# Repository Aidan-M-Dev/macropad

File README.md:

# IC Hack macropad

Six-key USB macropad with an OLED, addressable LEDs and a printable enclosure.

**Editing the appearance?** Start with the [artist handoff guide](appearance/README.md), or download the [self-contained handoff ZIP](build/appearance-handoff.zip). The [`appearance/`](appearance/) folder contains the colour config, PNG templates and image drop folder. No KiCad knowledge is needed.

The [reinforced frame](build/exports/top-frame-reinforced.stl) is the only frame version. It has **14.0 × 14.75 mm slots** (left/right × top/bottom), **6 mm straight standoffs with 0.8 mm walls**, a **flat 1 mm plate**, **2 mm links** and **2.4 mm mounting arms**. It uses the existing compact base, four **M3 × 12 mm socket-cap screws**, four M3 nuts and **no separate washers**. The flat top has no screw-head recesses; slimmer standoffs and smaller mounting pads reduce material use.

The updated [base](build/exports/base-m3x6.stl) has the USB opening's top lowered by **3 mm**, giving a **10.4 × 3.8 mm opening**. The bottom stays in place. See the [case guide](case/README.md) for connector fit and printing details.

[Exploded assembly](build/previews/top-frame-reinforced-exploded.png) · [Screw cross-section](build/previews/frame-cross-section.png) · [Printing and assembly](case/TOP-FRAME.md)

## Layout

| Folder | What belongs here |
| --- | --- |
| [`hardware/`](hardware/) | KiCad project, schematic, PCB and supplied STEP reference |
| [`case/`](case/README.md) | Enclosure CAD and presets |
| [`appearance/`](appearance/README.md) | Teammate handoff: hex colours, image drop folder and PNG guides |
| [`accessories/`](accessories/README.md) | Printable washers and M3 nut-fit tester |
| [`firmware/`](firmware/README.md) | Custom on-device software, board pin map and bring-up notes |
| `tools/` | Shared Python build, rendering and verification scripts |
| `build/` | Generated meshes, renders, reports, CAD inputs and supplier artwork |

The original ZIP is kept in `hardware/original/`. Edit the unpacked KiCad project in `hardware/`.

## Development commands

Run commands from this folder. The existing system Python packages work on this machine. For a separate environment elsewhere:

```bash
python3 -m venv .venv
. .venv/bin/activate
python -m pip install -r requirements.txt
```

The CAD workflow needs Python 3.10+, OpenSCAD, GNU Make 4.3+, and the DejaVu Sans font used by the renderer. Python requirements are listed in [`requirements.txt`](requirements.txt); firmware tools are separate.

```bash
make prepare   # Generate CAD inputs before opening OpenSCAD
make build     # Export printable parts and run exact clearance checks
make preview   # Build as needed, then refresh renders and supplier artwork
make check     # Refresh previews, then run the full design checks
make board     # Render front/back PCB images
make templates # Regenerate the artist’s PNG guides and blank canvases
make top-frame # Build and preview the reinforced switch retaining top
make firmware  # Build combined keyboard/Pong/Breakout/Doom UF2 (PlatformIO)
make firmware-clean  # Remove firmware build output; keep cached dependencies
make all       # Full design checks, board images and firmware build
```

`make` lists the commands. Set `PYTHON=/path/to/python` to use another interpreter, or `PIO=/path/to/pio` to select PlatformIO. See the [firmware installation instructions](firmware/README.md#building) before building firmware. The Makefile handles the order; PCB edits automatically refresh extracted geometry, and colour/artwork edits reuse existing meshes. Deleting a required mesh triggers a rebuild. Use `make clean` to remove generated build output, then `make all` to reproduce it. Firmware dependency caches are retained.

## What to edit

- **PCB/electronics:** open `hardware/IC Hack Macro Pad.kicad_pro`. Run `make preview` afterwards and update the firmware pin map if wiring changed. The supplied STEP file is a reference export, not automatically regenerated.
- **Enclosure dimensions:** edit `case/macropad_case.scad`, then run `make check`. Existing dimensional checks encode the current design; deliberate dimension changes may require updating their expected measurements.
- **OpenSCAD preview:** run `make prepare`, then open `case/macropad_case.scad` and select a preset. `base-m3x6.scad` opens the existing compact printable base. The reinforced frame uses M3 × 12 mm screws.
- **Accessories:** open an entry point in `accessories/`. Accessory modules share the enclosure's fastener dimensions so fit stays consistent.
- **Colours, keycap images and PCB artwork:** edit `appearance/config.json` and images in `appearance/images/`, then run `make preview`. See [appearance notes](case/APPEARANCE.md).
- **Custom software:** start in [`firmware/`](firmware/README.md); the pin map is taken from this PCB.

## Outputs

| Path | Contents |
| --- | --- |
| `firmware/.pio/build/ichack/ichack-combined.uf2` | Combined keyboard, Pong, Breakout and Doom firmware |
| `build/exports/base-m3x6.stl` | Existing compact base for the reinforced frame |
| `build/exports/top-frame-reinforced.stl` | [Reinforced retaining top; no separate washers](case/TOP-FRAME.md) |
| `build/exports/accessories/` | Printable washers and nut-fit tester |
| `build/exports/keycap.stl` | Printable keycap copied from the clicker project |
| `build/previews/` | Current frame assemblies, exploded view, cross-section and reference meshes |
| `build/exports/*-checks.json` | Verification reports |
| `build/exports/logs/` | OpenSCAD export and clearance logs |
| `build/print-pack/` | Keycap artwork, manifest and supplier CSV |
| `build/appearance-handoff.zip` | Self-contained artist handoff, also available as the `appearance/` folder |
| `build/board/` | Front/back PCB PNG and SVG |
| `build/generated/` | Extracted board datums, silkscreen and generated CAD colours |

Everything under `build/` can be regenerated. Current printable exports, previews, check reports, PCB images and the artwork pack are checked in so they can be viewed and downloaded directly. Intermediate CAD inputs, reference meshes, caches and logs are ignored. Keep source changes outside `build/`. See the [case guide](case/README.md) for printing and assembly details.

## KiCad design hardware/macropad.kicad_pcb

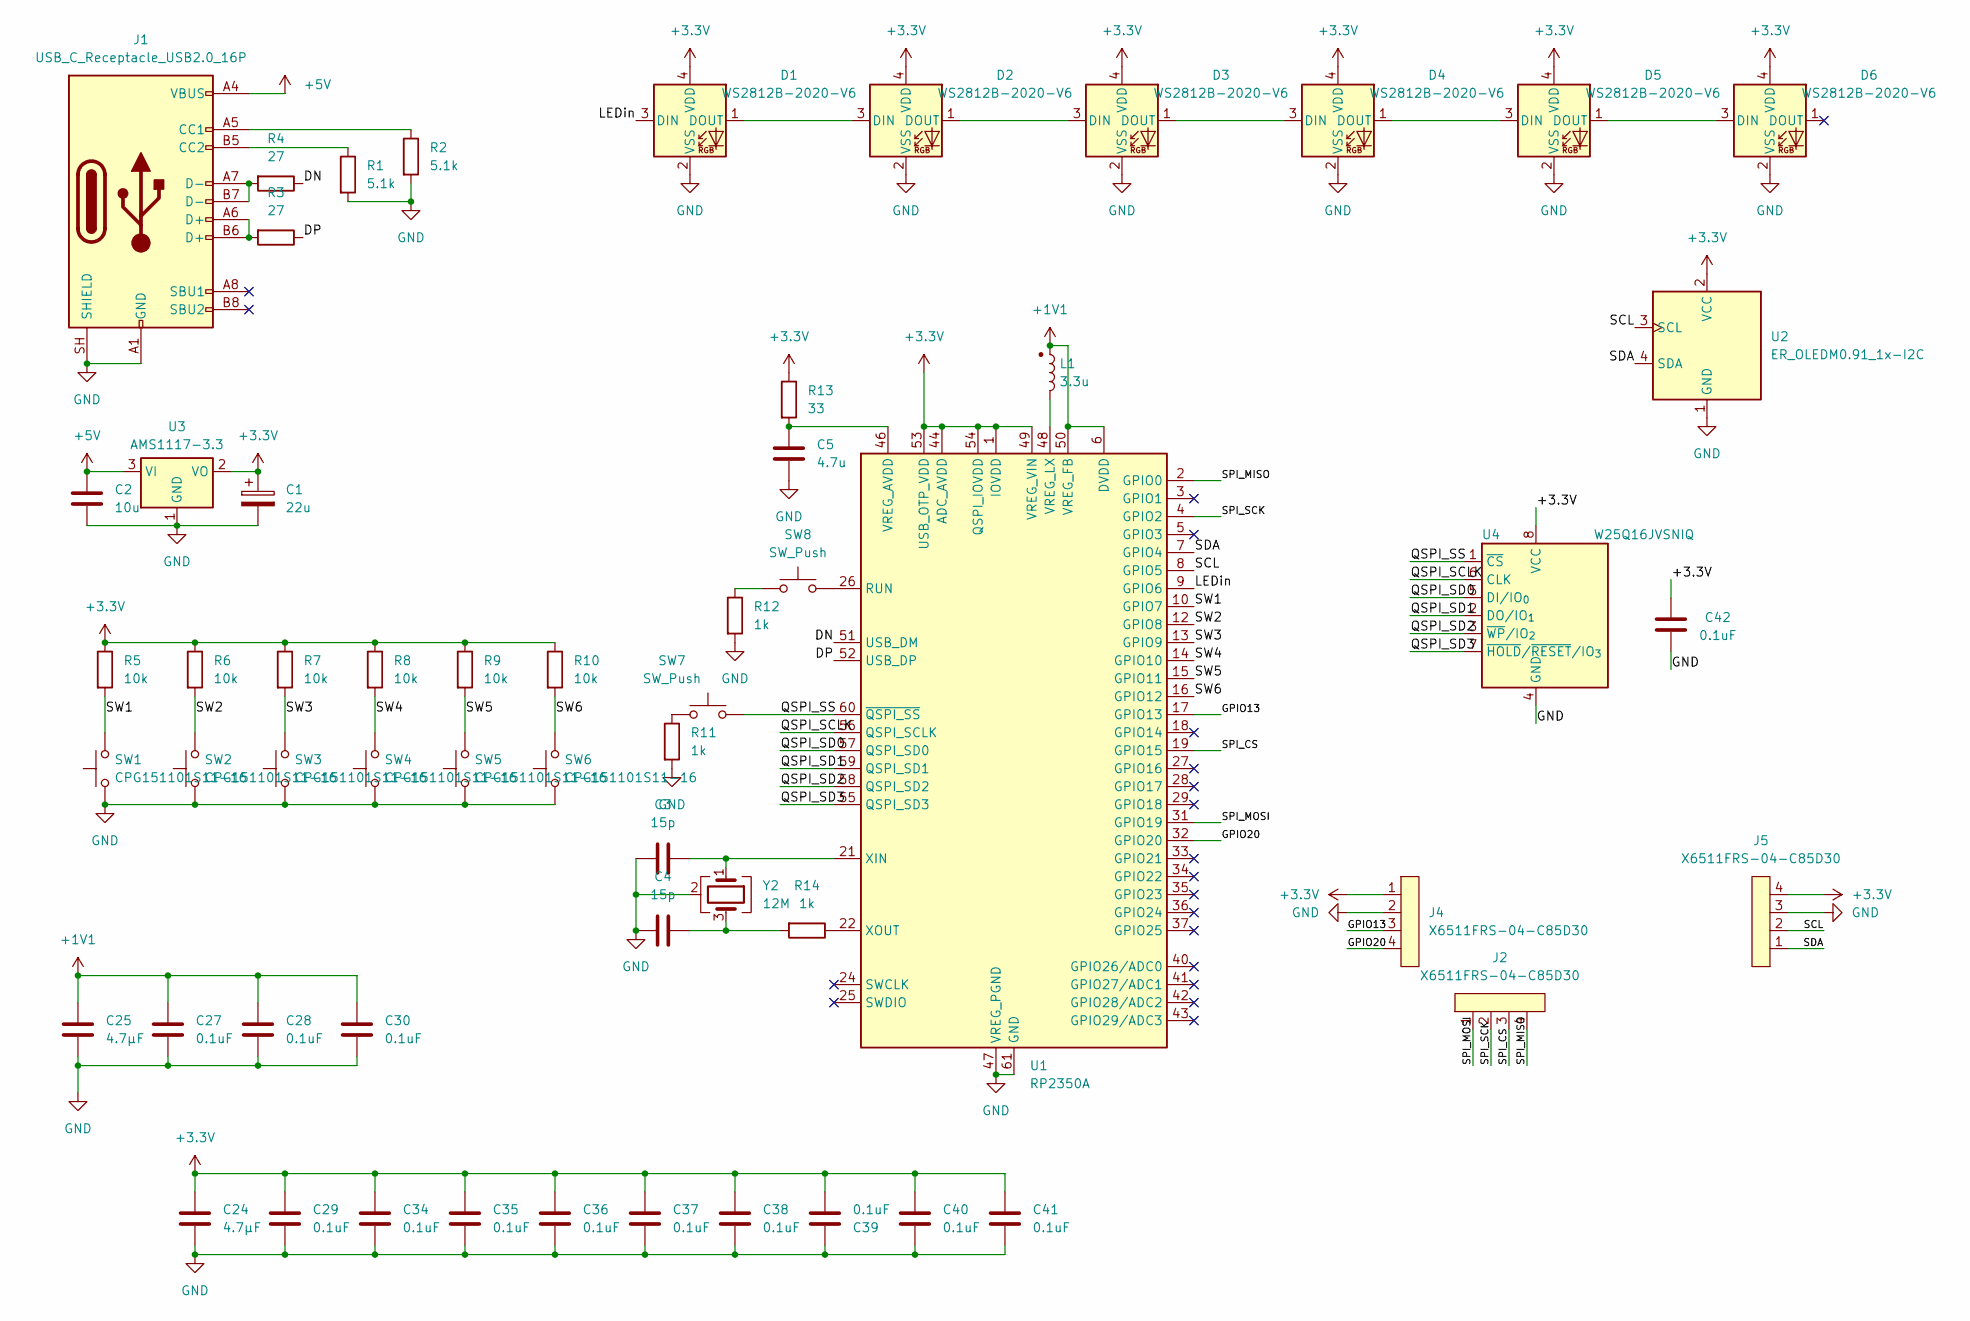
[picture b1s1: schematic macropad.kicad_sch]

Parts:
C1: 22u; CP_EIA-3528-21_Kemet-B; Voltage 16V; MPN TAJB226K016RNJ; LCSC Part # C8020
C2: 10u; C_0805_2012Metric; Voltage 10V minimum
C3, C4: 15p; C_0402_1005Metric; Voltage 16V minimum
C5: 4.7u; C_0402_1005Metric; Voltage 6.3V minimum
C24, C25: 4.7μF; C_0402_1005Metric; Voltage 6.3V minimum
C27, C28, C29, C30, C34, C35, C36, C37, C38, C39, C40, C41: 0.1uF; C_0402_1005Metric; Voltage 25V; MPN CL05B104KA5NNNC; LCSC Part # C155422
C42: 0.1uF; C_0402_1005Metric; MPN CL05B104KA5NNNC; LCSC Part # C155422
D1, D2, D3, D4, D5, D6: WS2812B-2020-V6; LED_WS2812B-2020_PLCC4_2.0x2.0mm; MPN WS2812B-2020-V6; LCSC Part # C52917434
J1: USB_C_Receptacle_USB2.0_16P; USB_C_Receptacle_HRO_TYPE-C-31-M-12; MPN TYPE-C-31-M-12; LCSC Part # C165948
J2, J4, J5: X6511FRS-04-C85D30; LCSC Part # C5142237
L1: 3.3u; L_Wuerth_PMCI-201610; MPN AOTA-B201610S3R3-101-T; LCSC Part # C42411119
R1, R2: 5.1k; R_0402_1005Metric
R3, R4: 27; R_0402_1005Metric
R5, R6, R7, R8, R9, R10: 10k; R_0402_1005Metric
R11, R12, R14: 1k; R_0402_1005Metric
R13: 33; R_0402_1005Metric
SW1, SW2, SW3, SW4, SW5, SW6: CPG151101S11-16; SW_Hotswap_Kailh_MX_1.00u; MPN CPG151101S11-16; LCSC Part # C41430893
SW7, SW8: SW_Push; SW_SPST_TS-1088-xR020; MPN TS-1088-AR02016; LCSC Part # C720477
U1: RP2350A; QFN-60-1EP_7x7mm_P0.4mm_EP3.4x3.4mm; MPN RP2350A; LCSC Part # C42411118
U2: ER_OLEDM0.91_1x-I2C; ER_OLEDM0.91_1x-I2C_Staggered_Offset0.175mm
U3: AMS1117-3.3; SOT-223-3_TabPin2; MPN AMS1117-3.3; LCSC Part # C6186
U4: W25Q16JVSNIQ; SOIC-8_3.9x4.9mm_P1.27mm; MPN W25Q16JVSNIQ; LCSC Part # C2456211
Y2: 12M; Crystal_SMD_3225-4Pin_3.2x2.5mm; MPN ABM8-272-T3; LCSC Part # C20625731

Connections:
+1V1: C25.1, C27.2, C28.2, C30.2, L1.1, U1.6 (DVDD), U1.23 (DVDD), U1.39 (DVDD), U1.50 (VREG_FB)
+3.3V: C1.1, C24.1, C29.2, C34.2, C35.2, C36.2, C37.2, C38.2, C39.1, C40.2, C41.2, C42.1, D1.4 (VDD), D2.4 (VDD), D3.4 (VDD), D4.4 (VDD), D5.4 (VDD), D6.4 (VDD), J4.1, J5.4, R5.1, R6.1, R7.1, R8.1, R9.1, R10.1, R13.1, U1.1 (IOVDD), U1.11 (IOVDD), U1.20 (IOVDD), U1.30 (IOVDD), U1.38 (IOVDD), U1.44 (ADC_AVDD), U1.45 (IOVDD), U1.49 (VREG_VIN), U1.53 (USB_OTP_VDD), U1.54 (QSPI_IOVDD), U2.2 (VCC), U3.2 (VO), U4.8 (VCC)
+5V: C2.1, J1.A4 (VBUS), J1.A9 (VBUS), J1.B4 (VBUS), J1.B9 (VBUS), U3.3 (VI)
/DN: R4.1, U1.51 (USB_DM)
/DP: R3.1, U1.52 (USB_DP)
/GPIO13: J4.3, U1.17 (GPIO13)
/GPIO20: J4.4, U1.32 (GPIO20)
/LEDin: D1.3 (DIN), U1.9 (GPIO6)
/QSPI_SCLK: U1.56 (QSPI_SCLK), U4.6 (CLK)
/QSPI_SD0: U1.57 (QSPI_SD0), U4.5 (DI/IO_{0})
/QSPI_SD1: U1.59 (QSPI_SD1), U4.2 (DO/IO_{1})
/QSPI_SD2: U1.58 (QSPI_SD2), U4.3 (~WP/IO_{2})
/QSPI_SD3: U1.55 (QSPI_SD3), U4.7 (~HOLD/~RESET/IO_{3})
/QSPI_SS: SW7.2, U1.60 (~QSPI_SS), U4.1 (~CS)
/SCL: J5.2, U1.8 (GPIO5), U2.3 (SCL)
/SDA: J5.1, U1.7 (GPIO4), U2.4 (SDA)
/SPI_CS: J2.3, U1.19 (GPIO15)
/SPI_MISO: J2.4, U1.2 (GPIO0)
/SPI_MOSI: J2.1, U1.31 (GPIO19)
/SPI_SCK: J2.2, U1.4 (GPIO2)
/SW1: R5.2, SW1.2, U1.10 (GPIO7)
/SW2: R6.2, SW2.2, U1.12 (GPIO8)
/SW3: R7.2, SW3.2, U1.13 (GPIO9)
/SW4: R8.2, SW4.2, U1.14 (GPIO10)
/SW5: R9.2, SW5.2, U1.15 (GPIO11)
/SW6: R10.2, SW6.2, U1.16 (GPIO12)
GND: C1.2, C2.2, C3.1, C4.1, C5.2, C24.2, C25.2, C27.1, C28.1, C29.1, C30.1, C34.1, C35.1, C36.1, C37.1, C38.1, C39.2, C40.1, C41.1, C42.2, D1.2 (VSS), D2.2 (VSS), D3.2 (VSS), D4.2 (VSS), D5.2 (VSS), D6.2 (VSS), J1.A1 (GND), J1.A12 (GND), J1.B1 (GND), J1.B12 (GND), J1.SH (SHIELD), J4.2, J5.3, R1.2, R2.2, R11.2, R12.2, SW1.1, SW2.1, SW3.1, SW4.1, SW5.1, SW6.1, U1.47 (VREG_PGND), U1.61 (GND), U2.1 (GND), U3.1 (GND), U4.4 (GND), Y2.2 (G), Y2.4 (G)
unnamed: C4.2, R14.2, Y2.3
unnamed: D1.1 (DOUT), D2.3 (DIN)
unnamed: D2.1 (DOUT), D3.3 (DIN)
unnamed: D3.1 (DOUT), D4.3 (DIN)
unnamed: D4.1 (DOUT), D5.3 (DIN)
unnamed: D5.1 (DOUT), D6.3 (DIN)
unnamed: J1.A5 (CC1), R2.1
unnamed: J1.B5 (CC2), R1.1
unnamed: J1.A6 (D+), J1.B6 (D+), R3.2
unnamed: J1.A7 (D-), J1.B7 (D-), R4.2
unnamed: R11.1, SW7.1
unnamed: R12.1, SW8.1
unnamed: SW8.2, U1.26 (RUN)
unnamed: C5.1, R13.2, U1.46 (VREG_AVDD)
unnamed: L1.2, U1.48 (VREG_LX)
unnamed: C3.2, U1.21 (XIN), Y2.1
unnamed: R14.1, U1.22 (XOUT)

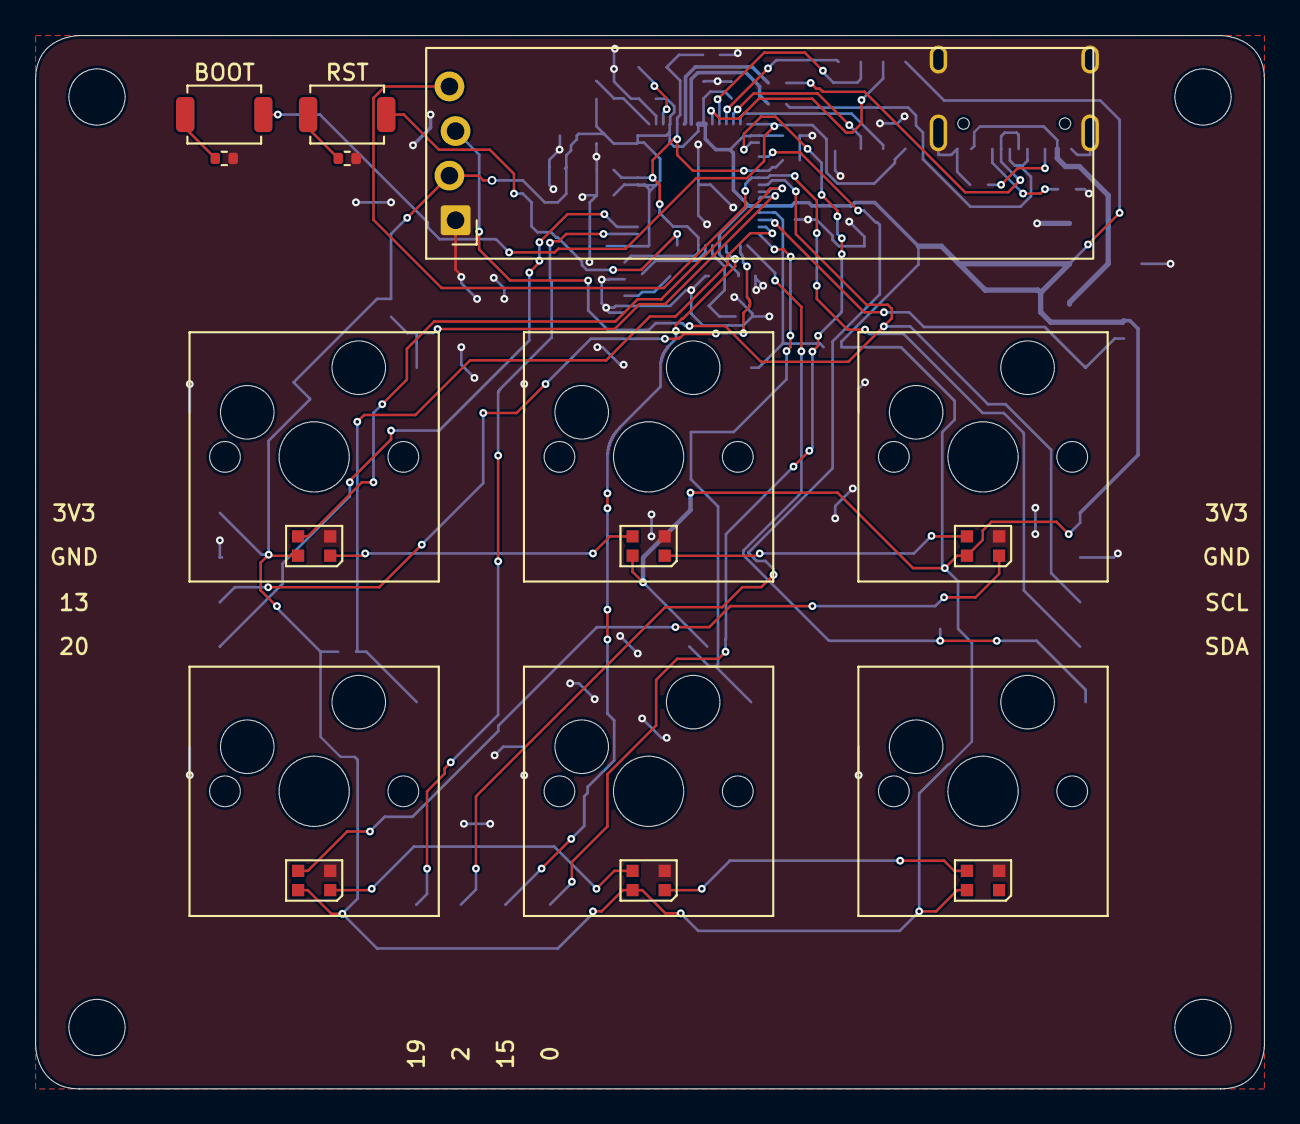
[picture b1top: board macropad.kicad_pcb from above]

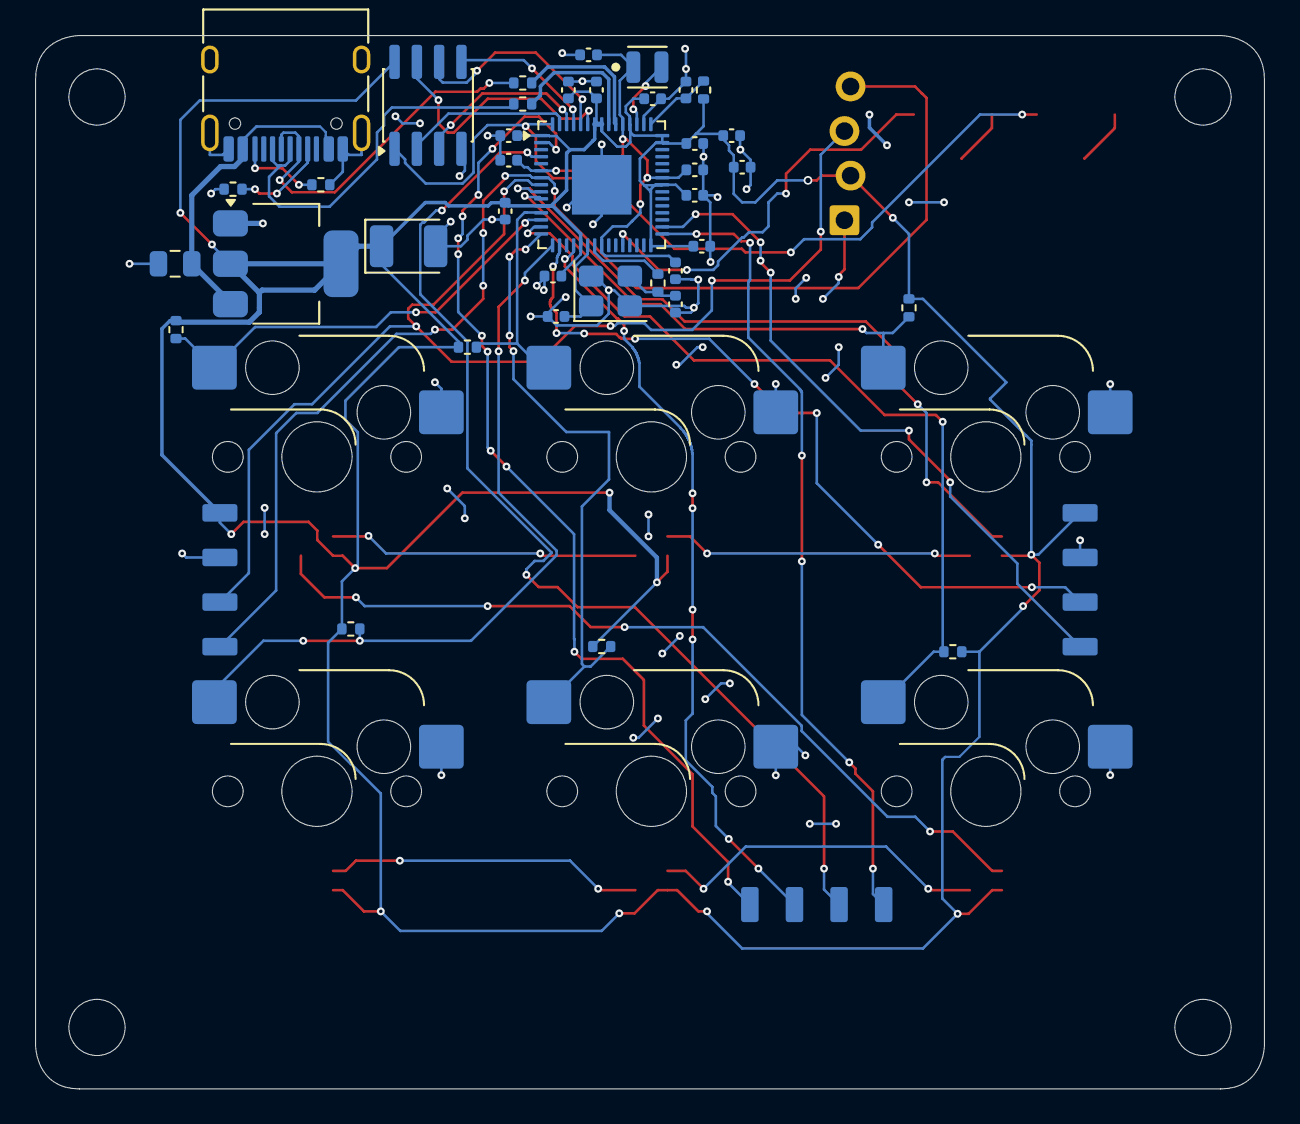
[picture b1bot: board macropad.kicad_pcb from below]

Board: 2 copper layers, 70.0 x 60.0 mm, 62 parts (41 on the bottom side), 44 nets.

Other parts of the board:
H1, H2, H3, H4: MountingHole_3.2mm_M3
